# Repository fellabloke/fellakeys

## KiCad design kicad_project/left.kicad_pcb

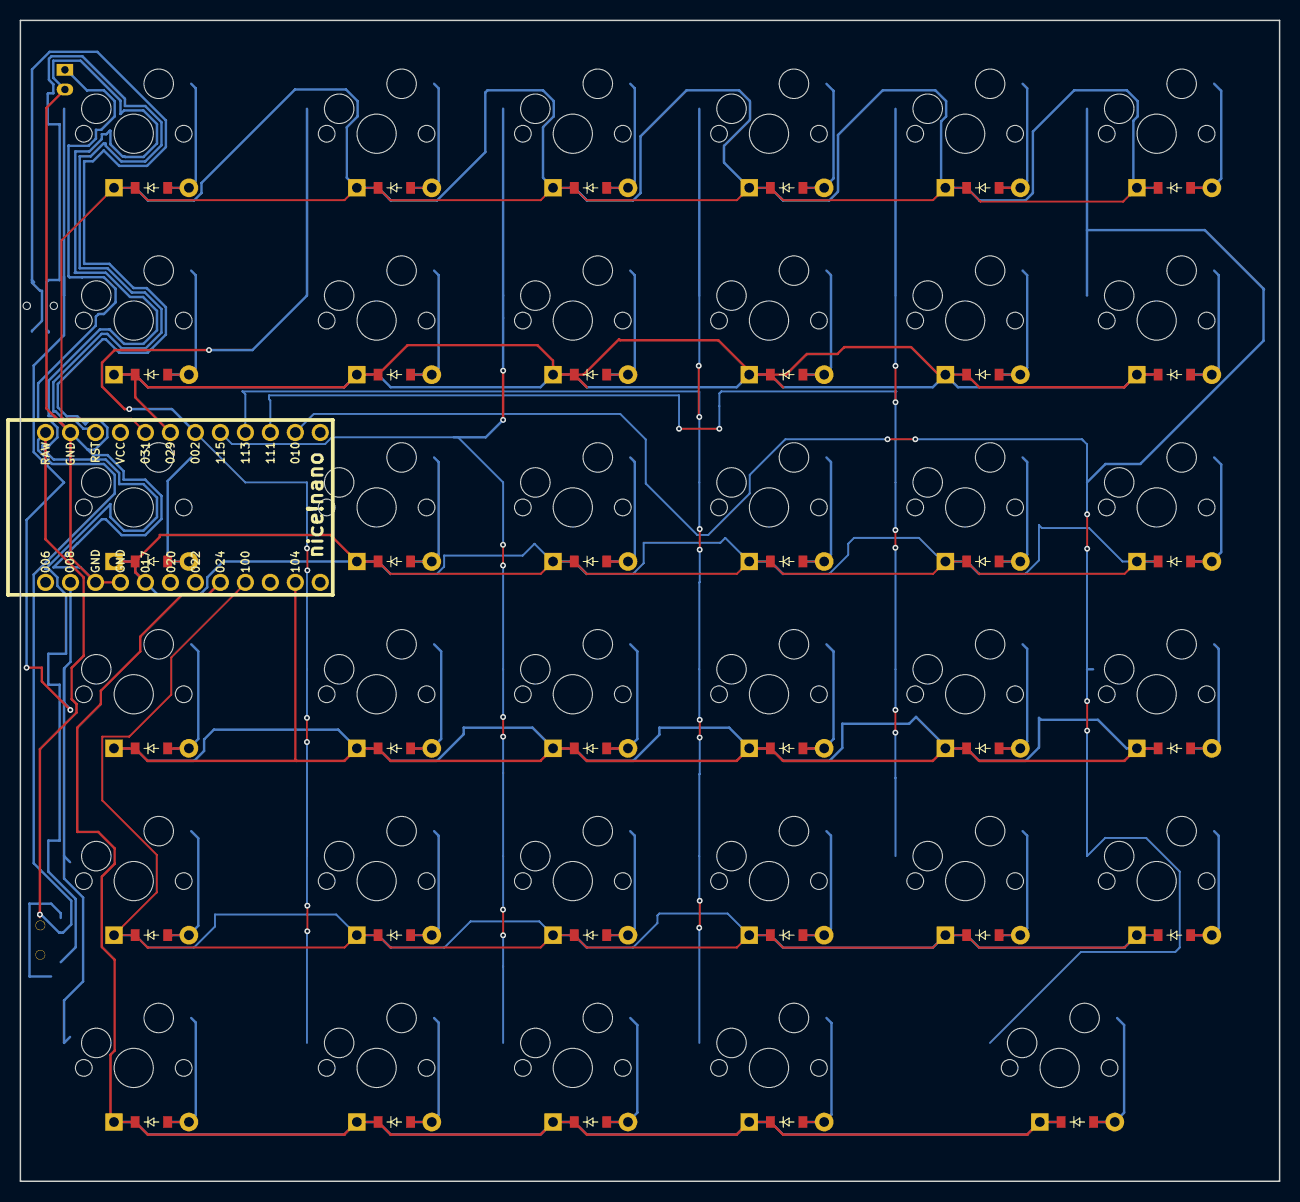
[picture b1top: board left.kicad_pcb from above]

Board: 2 copper layers, 128.1 x 118.1 mm, 74 parts (0 on the bottom side), 51 nets.

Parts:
B1: Panasonic_EVQPUL_EVQPUC
D1, D2, D3, D4, D5, D6, D7, D8, D9, D10, D11, D12, D13, D14, D15, D16, D17, D18, D19, D20, D21, D22, D23, D24, D25, D26, D27, D28, D29, D30, D31, D32, D33, D34, D35: ComboDiode
JST1: JST_PH_S2B-PH-K_02x2.00mm_Angled
MCU1: nice_nano
S1, S2, S3, S4, S5, S6, S7, S8, S9, S10, S11, S12, S13, S14, S15, S16, S17, S18, S19, S20, S21, S22, S23, S24, S25, S26, S27, S28, S29, S30, S31, S32, S33, S34, S35: MX
T1: SPDT_C128955

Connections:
GND: B1.1, JST1.2, MCU1.3, MCU1.4, MCU1.23
P002: MCU1.18, S7.1, S8.1, S9.1, S10.1, S11.1, S12.1
P008: MCU1.2, S1.1, S2.1, S3.1, S4.1, S5.1, S6.1
P010: MCU1.14, S30.1, S31.1, S32.1, S33.1, S34.1, S35.1
P017: D4.1, D10.1, D16.1, D22.1, D27.1, D32.1, MCU1.5
P024: D1.1, D7.1, D13.1, D19.1, D35.1, MCU1.8
P029: D5.1, D11.1, D17.1, D23.1, D28.1, D33.1, MCU1.19
P031: D6.1, D12.1, D18.1, D24.1, D29.1, D34.1, MCU1.20
P100: D2.1, D8.1, D14.1, D20.1, D25.1, D30.1, MCU1.9
P104: D3.1, D9.1, D15.1, D21.1, D26.1, D31.1, MCU1.11
P111: MCU1.15, S25.1, S26.1, S27.1, S28.1, S29.1
P113: MCU1.16, S19.1, S20.1, S21.1, S22.1, S23.1, S24.1
P115: MCU1.17, S13.1, S14.1, S15.1, S16.1, S17.1, S18.1
RAW: MCU1.24, T1.2
RST: B1.2, MCU1.22
default_default: D35.2, S35.2
index_bottom: D20.2, S20.2
index_bottombottom: D19.2, S19.2
index_fn: D24.2, S24.2
index_home: D21.2, S21.2
index_num: D23.2, S23.2
index_top: D22.2, S22.2
inner_bottom: D25.2, S25.2
inner_fn: D29.2, S29.2
inner_home: D26.2, S26.2
inner_num: D28.2, S28.2
inner_top: D27.2, S27.2
innerinner_bottom: D30.2, S30.2
innerinner_fn: D34.2, S34.2
innerinner_home: D31.2, S31.2
innerinner_num: D33.2, S33.2
innerinner_top: D32.2, S32.2
middle_bottom: D14.2, S14.2
middle_bottombottom: D13.2, S13.2
middle_fn: D18.2, S18.2
middle_home: D15.2, S15.2
middle_num: D17.2, S17.2
middle_top: D16.2, S16.2
pinky_bottom: D2.2, S2.2
pinky_bottombottom: D1.2, S1.2
pinky_fn: D6.2, S6.2
pinky_home: D3.2, S3.2
pinky_num: D5.2, S5.2
pinky_top: D4.2, S4.2
pos: JST1.1, T1.1
ring_bottom: D8.2, S8.2
ring_bottombottom: D7.2, S7.2
ring_fn: D12.2, S12.2
ring_home: D9.2, S9.2
ring_num: D11.2, S11.2
ring_top: D10.2, S10.2

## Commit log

2025-07-21 please
